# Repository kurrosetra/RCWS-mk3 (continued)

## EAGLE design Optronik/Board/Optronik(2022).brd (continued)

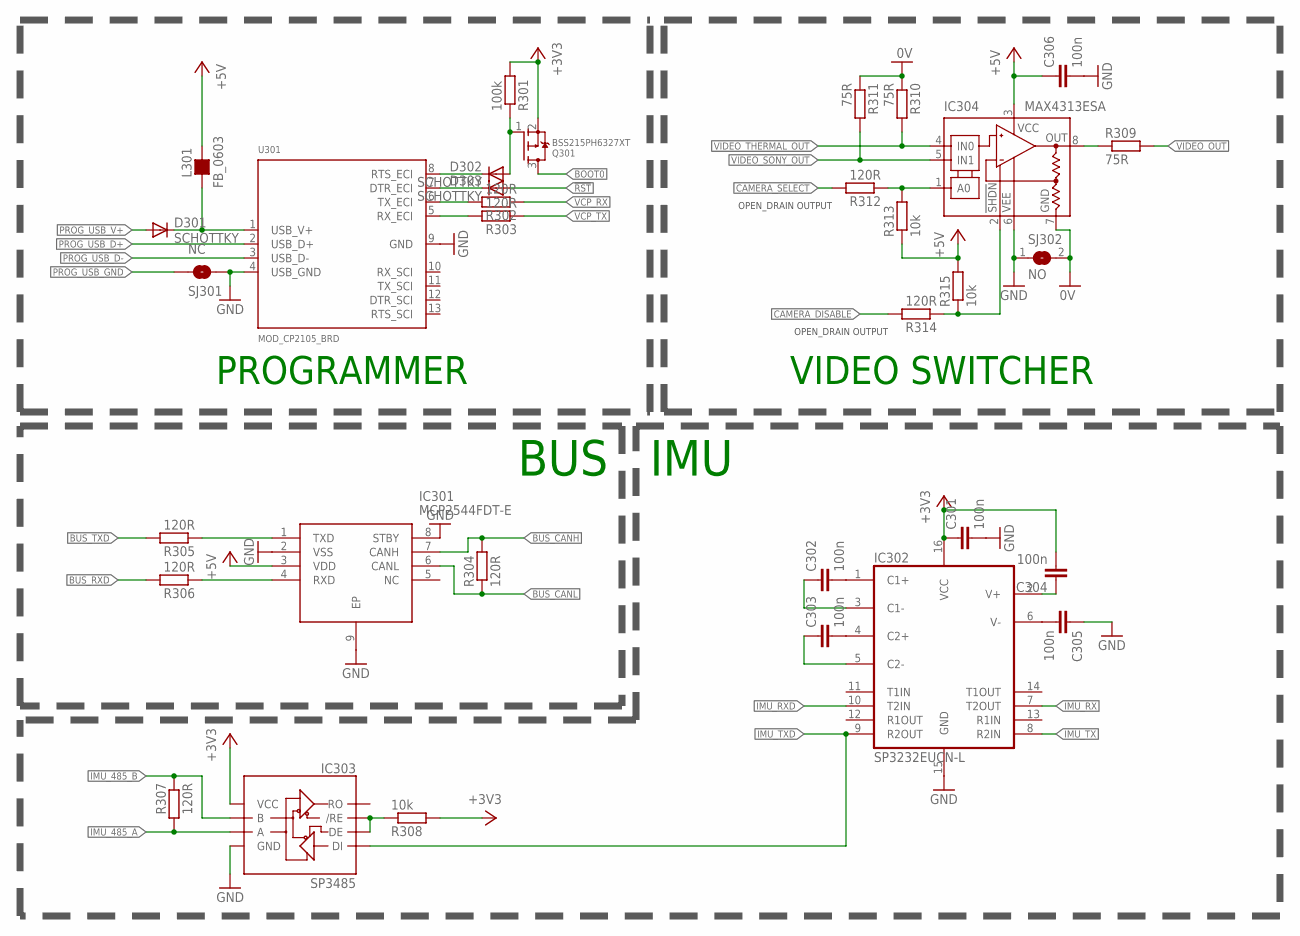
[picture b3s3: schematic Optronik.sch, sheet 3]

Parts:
C301, C302, C303, C304, C305, C306: 100n; C0603
D301, D302, D303: SCHOTTKY; MICROMELF-W
IC301: MCP2544FDT-E; TDFN-8
IC302: SP3232EUCN-L; SO016
IC303: SP3485; SO08
IC304: MAX4313ESA; SO08
L301: FB_0603; L0603
Q301: BSS215PH6327XT; SOT23-W
R301: 100k; R0603
R302, R303, R304, R305, R306, R307, R312, R314: 120R; R0603
R308, R313, R315: 10k; R0603
R309, R310, R311: 75R; R0603
SJ301: NC; SJ_2S-TRACE_THICK
SJ302: NO; SJS
U301: MOD_CP2105_BRD; MOD_CP2105_BOARD

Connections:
0V: IC304.7 (GND), R310.1, R311.1, SJ302.2; also elsewhere on the board
!RST: D303.A; also elsewhere on the board
+3V3: C301.1, C304.2, IC302.16 (VCC), IC303.8 (VCC), Q301.2 (S), R301.2, R308.2; also elsewhere on the board
+5V: C306.1, IC301.3 (VDD), IC304.3 (V+), L301.2, R313.1, R315.2; also elsewhere on the board
BOOT0: Q301.3 (D); also elsewhere on the board
BUS_CANH: IC301.7 (CANH), R304.2; also elsewhere on the board
BUS_CANL: IC301.6 (CANL), R304.1; also elsewhere on the board
BUS_RXD: R306.2; also elsewhere on the board
BUS_TXD: R305.2; also elsewhere on the board
CAMERA_DISABLE: R314.2; also elsewhere on the board
CAMERA_SELECT: R312.2; also elsewhere on the board
GND: C301.2, C305.1, C306.2, IC301.2 (VSS), IC301.8 (STBY), IC301.9 (EP), IC302.15 (GND), IC303.5 (GND), IC304.6 (V-), SJ301.2, SJ302.1, U301.4 (USB_GND), U301.9 (GND); also elsewhere on the board
IMU_485_A: IC303.6 (A), R307.2; also elsewhere on the board
IMU_485_B: IC303.7 (B), R307.1; also elsewhere on the board
IMU_RX: IC302.7 (T2OUT); also elsewhere on the board
IMU_RXD: IC302.10 (T2IN); also elsewhere on the board
IMU_TX: IC302.8 (R2IN); also elsewhere on the board
IMU_TXD: IC302.9 (R2OUT), IC303.4 (DI); also elsewhere on the board
unnamed: IC303.2 (/RE), IC303.3 (DE), R308.1
unnamed: IC304.1 (A0), R312.1, R313.2
unnamed: IC301.1 (TXD), R305.1
unnamed: IC301.4 (RXD), R306.1
unnamed: R303.2, U301.5 (RX_ECI)
unnamed: R302.2, U301.6 (TX_ECI)
unnamed: D303.C, U301.7 (DTR_ECI)
unnamed: IC304.8 (OUT), R309.1
unnamed: D302.C, U301.8 (RTS_ECI)
unnamed: IC304.2 (!SHDN), R314.1, R315.1
unnamed: D301.C, L301.1, U301.1 (USB_V+)
unnamed: D302.A, Q301.1 (G), R301.1
unnamed: C305.2, IC302.6 (V-)
unnamed: C302.2, IC302.1 (C1+)
unnamed: C303.2, IC302.4 (C2+)
unnamed: C302.1, IC302.3 (C1-)
unnamed: C303.1, IC302.5 (C2-)
unnamed: C304.1, IC302.2 (V+)
PROG_USB_D+: U301.2 (USB_D+); also elsewhere on the board
PROG_USB_D-: U301.3 (USB_D-); also elsewhere on the board
PROG_USB_GND: SJ301.1; also elsewhere on the board
PROG_USB_V+: D301.A; also elsewhere on the board
VCP_RX: R302.1; also elsewhere on the board
VCP_TX: R303.1; also elsewhere on the board
VIDEO_OUT: R309.2; also elsewhere on the board
VIDEO_SONY_OUT: IC304.5 (IN1), R311.2; also elsewhere on the board
VIDEO_THERMAL_OUT: IC304.4 (IN0), R310.2; also elsewhere on the board

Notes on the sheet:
BUS
IMU
OPEN_DRAIN OUTPUT
PROGRAMMER
VIDEO SWITCHER

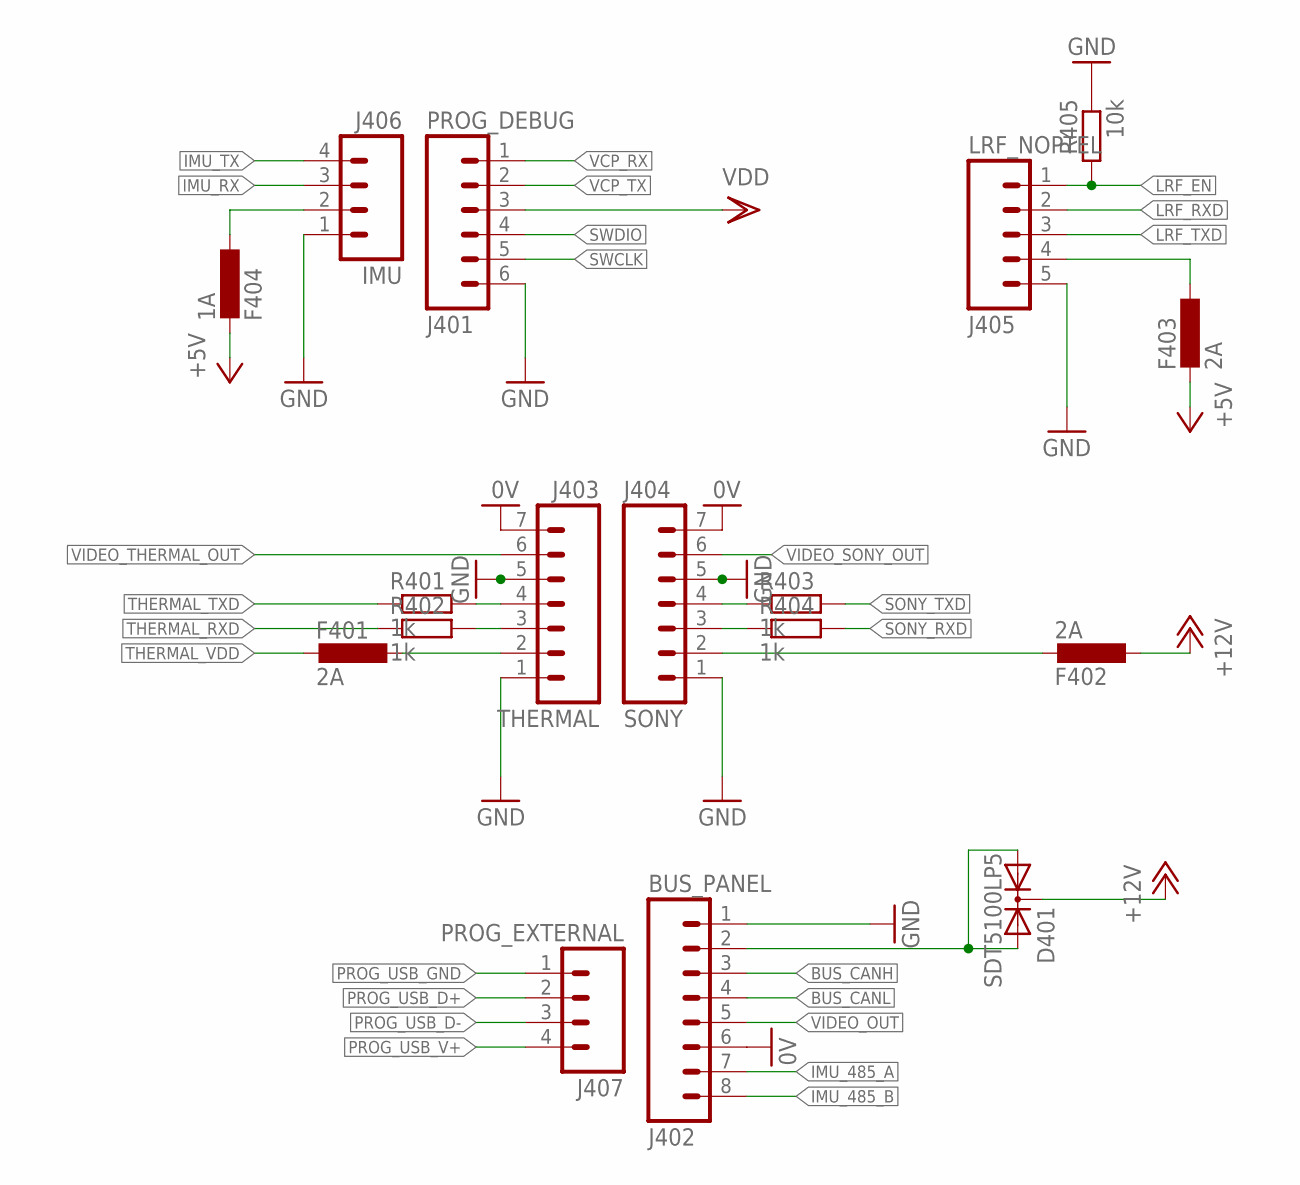
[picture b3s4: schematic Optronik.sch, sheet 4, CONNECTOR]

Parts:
D401: SDT5100LP5; POWERDI5-3
F401, F402, F403: 2A; L0805
F404: 1A; L0805
J401: PROG_DEBUG; XHS-6-VERT-SMD
J402: BUS_PANEL; XHS-8-RA
J403: THERMAL; XHS-7-RA
J404: SONY; XHS-7-RA
J405: LRF_NOPTEL; XHS-5-RA
J406: IMU; XHS-4-RA
J407: PROG_EXTERNAL; XHS-4-RA
R401, R402, R403, R404: 1k; R0603
R405: 10k; R0603

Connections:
0V: J402.6, J403.7, J404.7; also elsewhere on the board
!LRF_EN: J405.1, R405.2; also elsewhere on the board
+5V: F403.2, F404.2; also elsewhere on the board
+12V: D401.3, F402.1; also elsewhere on the board
BUS_CANH: J402.3; also elsewhere on the board
BUS_CANL: J402.4; also elsewhere on the board
GND: J401.6, J402.1, J403.1, J403.5, J404.1, J404.5, J405.5, J406.1, R405.1; also elsewhere on the board
IMU_485_A: J402.7; also elsewhere on the board
IMU_485_B: J402.8; also elsewhere on the board
IMU_RX: J406.3; also elsewhere on the board
IMU_TX: J406.4; also elsewhere on the board
LRF_RXD: J405.2; also elsewhere on the board
LRF_TXD: J405.3; also elsewhere on the board
unnamed: F403.1, J405.4
unnamed: F402.2, J404.2
unnamed: J403.4, R401.2
unnamed: F401.1, J403.2
unnamed: J403.3, R402.2
unnamed: J404.4, R403.1
unnamed: J404.3, R404.1
unnamed: F404.1, J406.2
PROG_USB_D+: J407.2; also elsewhere on the board
PROG_USB_D-: J407.3; also elsewhere on the board
PROG_USB_GND: J407.1; also elsewhere on the board
PROG_USB_V+: J407.4; also elsewhere on the board
RAW_12V: D401.1, D401.2, J402.2
SONY_RXD: R404.2; also elsewhere on the board
SONY_TXD: R403.2; also elsewhere on the board
SWCLK: J401.5; also elsewhere on the board
SWDIO: J401.4; also elsewhere on the board
THERMAL_RXD: R402.1; also elsewhere on the board
THERMAL_TXD: R401.1; also elsewhere on the board
THERMAL_VDD: F401.2; also elsewhere on the board
VCP_RX: J401.1; also elsewhere on the board
VCP_TX: J401.2; also elsewhere on the board
VDD: J401.3; also elsewhere on the board
VIDEO_OUT: J402.5; also elsewhere on the board
VIDEO_SONY_OUT: J404.6; also elsewhere on the board
VIDEO_THERMAL_OUT: J403.6; also elsewhere on the board

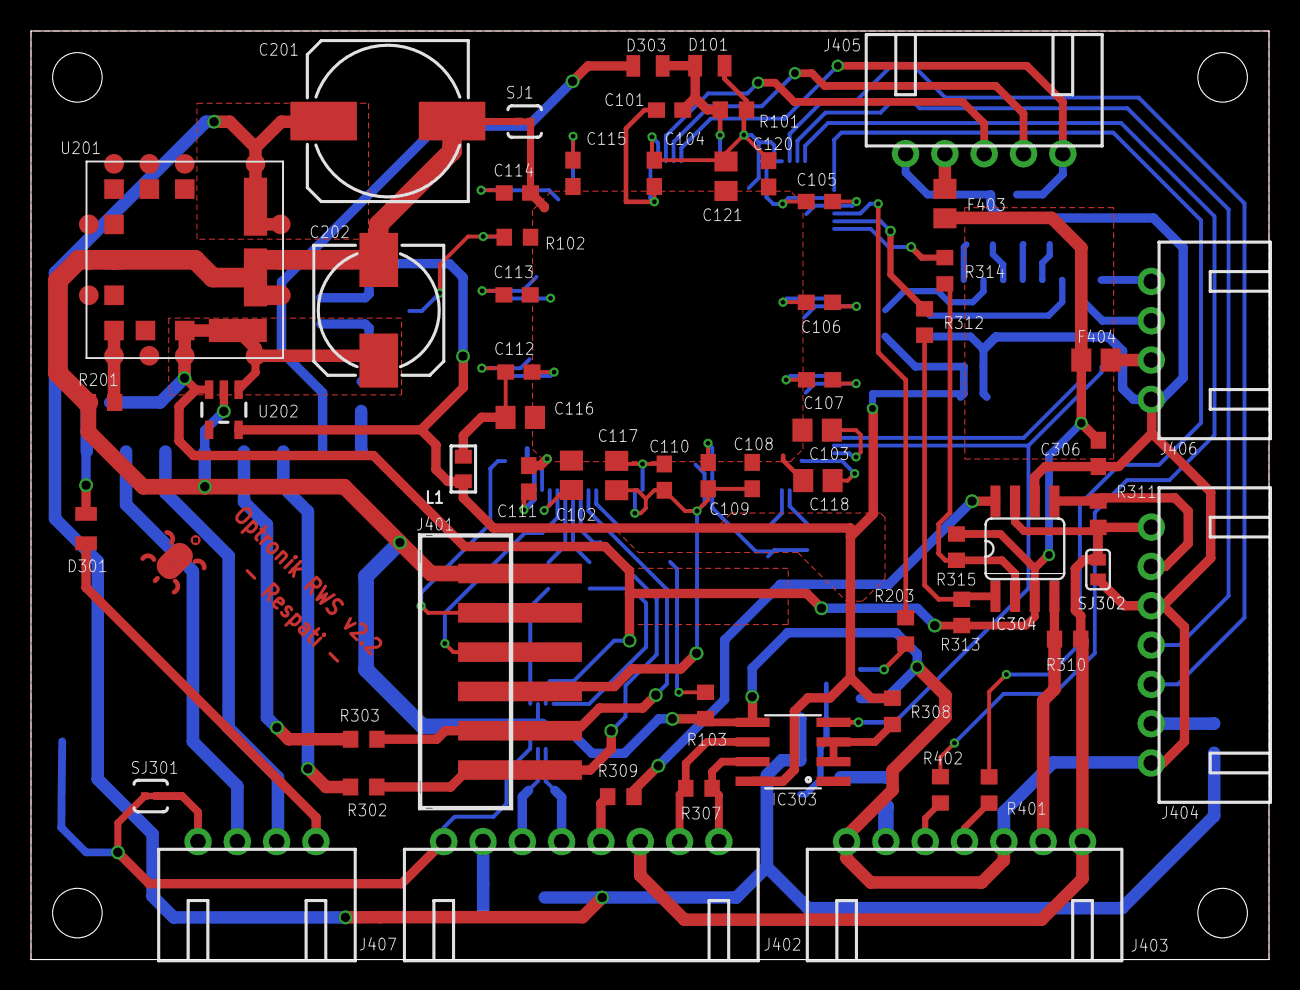
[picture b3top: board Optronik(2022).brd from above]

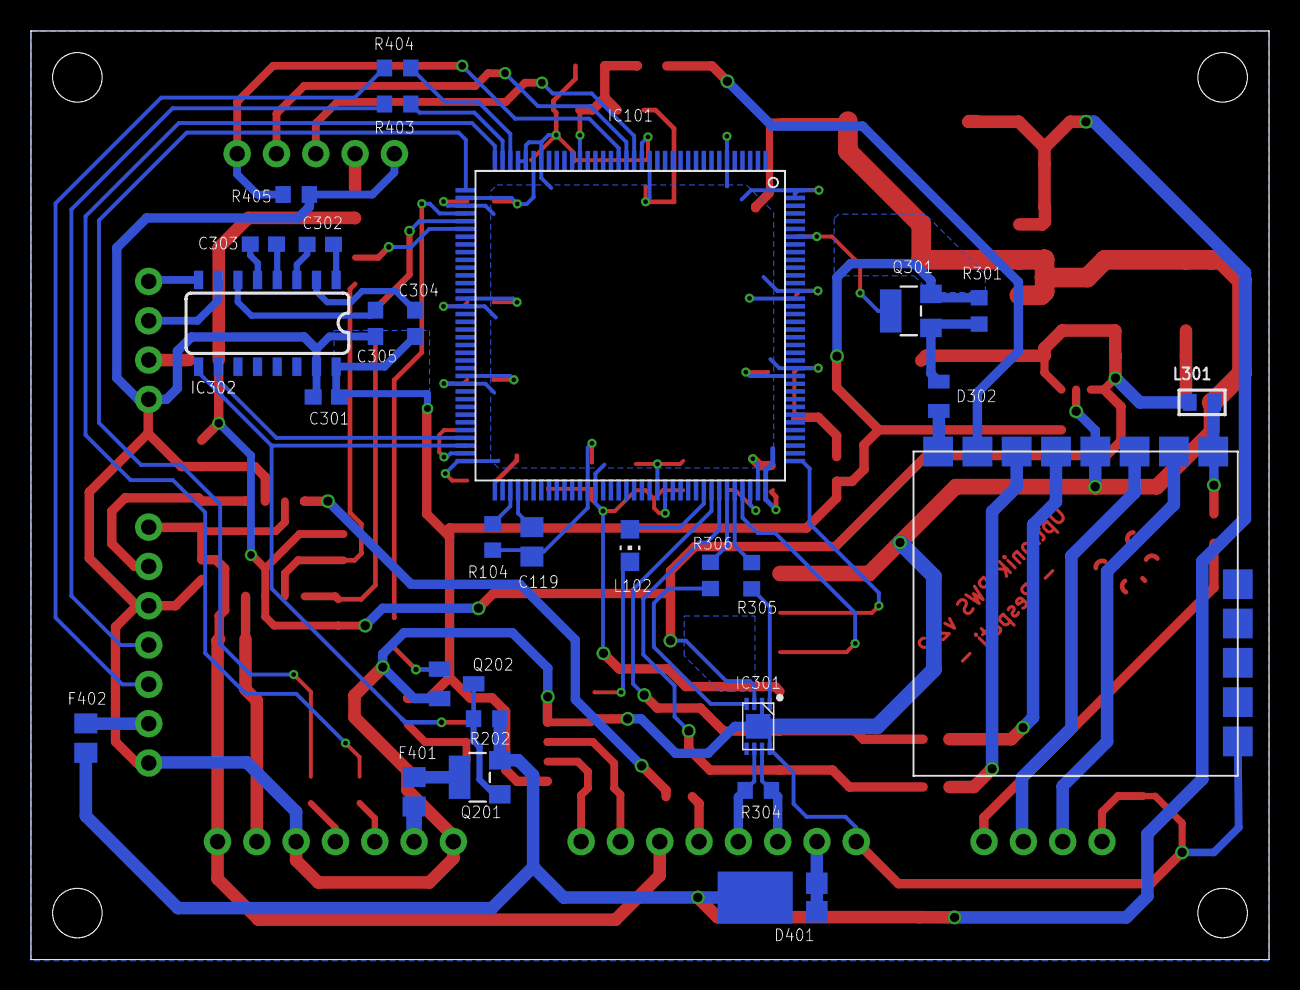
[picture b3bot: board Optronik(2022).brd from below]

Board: 2 copper layers, 80.0 x 60.0 mm, 90 parts (29 on the bottom side), 77 nets.

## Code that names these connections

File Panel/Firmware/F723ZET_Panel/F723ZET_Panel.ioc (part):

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Mcu.Name=STM32F723Z(C-E)Tx
Mcu.Package=LQFP144
Mcu.UserName=STM32F723ZETx
PA0-WKUP.GPIOParameters=GPIO_PuPd,GPIO_Label
PA0-WKUP.GPIO_Label=JSR_B
PA0-WKUP.GPIO_PuPd=GPIO_PULLUP
PA0-WKUP.Signal=GPIO_Input
PA1.GPIOParameters=GPIO_PuPd,GPIO_Label
PA1.GPIO_Label=JSR_TRIG
PA1.GPIO_PuPd=GPIO_PULLUP
PA1.Signal=GPIO_Input
PA10.GPIOParameters=GPIO_Label
PA10.GPIO_Label=VCP_RX
PA10.Mode=Asynchronous
PA10.Signal=USART1_RX
PA13.Mode=Serial_Wire
PA13.Signal=SYS_JTMS-SWDIO
PA14.Mode=Serial_Wire
PA14.Signal=SYS_JTCK-SWCLK
PA15.GPIOParameters=GPIO_Label
PA15.GPIO_Label=V_BATT_FREQ
PA15.Signal=S_TIM2_CH1_ETR
PA2.GPIOParameters=GPIO_Label
PA2.GPIO_Label=PC_S_RXD
PA2.Mode=Asynchronous
PA2.Signal=USART2_TX
PA3.GPIOParameters=GPIO_PuPd,GPIO_Label
PA3.GPIO_Label=PC_S_TXD
PA3.GPIO_PuPd=GPIO_PULLUP
PA3.Mode=Asynchronous
PA3.Signal=USART2_RX
PA4.GPIOParameters=GPIO_PuPd,GPIO_Label
PA4.GPIO_Label=JSL_DEADMAN
PA4.GPIO_PuPd=GPIO_PULLUP
PA4.Signal=GPIO_Input
PA5.GPIOParameters=GPIO_Label
PA5.GPIO_Label=JSL_AZIMUTH
PA5.Signal=ADCx_IN5
PA6.GPIOParameters=GPIO_Label
PA6.GPIO_Label=JSL_ELEVATION
PA6.Signal=ADCx_IN6
PA7.GPIOParameters=GPIO_PuPd,GPIO_Label
PA7.GPIO_Label=JSL_A
PA7.GPIO_PuPd=GPIO_PULLUP
PA7.Signal=GPIO_Input
PA8.GPIOParameters=GPIO_Label
PA8.GPIO_Label=LED_BUILTIN
PA8.Signal=GPIO_Output
PA9.GPIOParameters=GPIO_Label
PA9.GPIO_Label=VCP_TX
PA9.Mode=Asynchronous
PA9.Signal=USART1_TX
PB10.GPIOParameters=GPIO_Label
PB10.GPIO_Label=PC_E_RXD
PB10.Mode=Asynchronous
PB10.Signal=USART3_TX
PB11.GPIOParameters=GPIO_PuPd,GPIO_Label
PB11.GPIO_Label=PC_E_TXD
PB11.GPIO_PuPd=GPIO_PULLUP
PB11.Mode=Asynchronous
PB11.Signal=USART3_RX
PB2.Signal=QUADSPI_CLK
PB3.GPIOParameters=PinState,GPIO_PuPd,GPIO_Label,GPIO_ModeDefaultOutputPP
PB3.GPIO_Label=SLA_POWER_ENABLE
PB3.GPIO_ModeDefaultOutputPP=GPIO_MODE_OUTPUT_OD
PB3.GPIO_PuPd=GPIO_NOPULL
PB3.PinState=GPIO_PIN_SET
PB3.Signal=GPIO_Output
PB4.GPIOParameters=GPIO_PuPd,GPIO_Label
PB4.GPIO_Label=DUAL_TRIG_IN
PB4.GPIO_PuPd=GPIO_PULLUP
PB4.Signal=GPIO_Input
PB5.GPIOParameters=GPIO_Label
PB5.GPIO_Label=TRIG_PULSE_OUT
PB5.Signal=GPIO_Output
PB6.Signal=QUADSPI_BK1_NCS
PB8.Mode=CAN_Activate
PB8.Signal=CAN1_RX
PB9.Mode=CAN_Activate
PB9.Signal=CAN1_TX
PC0.GPIOParameters=GPIO_PuPd,GPIO_Label
PC0.GPIO_Label=JSR_DEADMAN
PC0.GPIO_PuPd=GPIO_PULLUP
PC0.Signal=GPIO_Input
PC1.GPIOParameters=GPIO_Label
PC1.GPIO_Label=JSR_AZIMUTH
PC1.Signal=ADCx_IN11
PC10.GPIOParameters=GPIO_Label
PC10.GPIO_Label=BMS_RXD
PC10.Signal=UART4_TX
PC11.GPIOParameters=GPIO_Label
PC11.GPIO_Label=BMS_TXD
PC11.Signal=UART4_RX
PC13.GPIOParameters=GPIO_Label
PC13.GPIO_Label=SYS_WKUP4
PC13.Signal=SYS_WKUP4
PC2.GPIOParameters=GPIO_Label
PC2.GPIO_Label=JSR_ELEVATION
PC2.Signal=ADCx_IN12
PC3.GPIOParameters=GPIO_PuPd,GPIO_Label
PC3.GPIO_Label=JSR_A
PC3.GPIO_PuPd=GPIO_PULLUP
PC3.Signal=GPIO_Input
PC4.GPIOParameters=GPIO_PuPd,GPIO_Label
PC4.GPIO_Label=JSL_B
PC4.GPIO_PuPd=GPIO_PULLUP
PC4.Signal=GPIO_Input
PC5.GPIOParameters=GPIO_PuPd,GPIO_Label
PC5.GPIO_Label=JSL_TRIG
PC5.GPIO_PuPd=GPIO_PULLUP
PC5.Signal=GPIO_Input
PC6.GPIOParameters=GPIO_Label
PC6.GPIO_Label=OUT_TRIGGER
PC6.Signal=GPIO_Output
PC7.GPIOParameters=GPIO_Label
PC7.GPIO_Label=OUT_POWER
PC7.Signal=GPIO_Output
PC8.GPIOParameters=GPIO_Label
PC8.GPIO_Label=OUT_CAMERA_SELECT
PC8.Signal=GPIO_Output
PC9.GPIOParameters=GPIO_Label
PC9.GPIO_Label=OUT_LRF_ENABLE
PC9.Signal=GPIO_Output
PD0.GPIOParameters=GPIO_PuPd,GPIO_Label
PD0.GPIO_Label=IN_LRF_START
PD0.GPIO_PuPd=GPIO_PULLUP
PD0.Signal=GPIO_Input
PD1.GPIOParameters=GPIO_PuPd,GPIO_Label
PD1.GPIO_Label=IN_LRF_MAN_UP
PD1.GPIO_PuPd=GPIO_PULLUP
PD1.Signal=GPIO_Input
PD2.GPIOParameters=GPIO_PuPd,GPIO_Label
PD2.GPIO_Label=IN_TRIGGER_ENABLE
PD2.GPIO_PuPd=GPIO_PULLUP
PD2.Signal=GPIO_Input
PD3.GPIOParameters=GPIO_PuPd,GPIO_Label
PD3.GPIO_Label=IN_FOCUS_FAR
PD3.GPIO_PuPd=GPIO_PULLUP
PD3.Signal=GPIO_Input
PD4.GPIOParameters=GPIO_PuPd,GPIO_Label
PD4.GPIO_Label=IN_TARGET_NEXT
PD4.GPIO_PuPd=GPIO_PULLUP
PD4.Signal=GPIO_Input
PD5.GPIOParameters=GPIO_PuPd,GPIO_Label
PD5.GPIO_Label=IN_FIRE_MODE1
PD5.GPIO_PuPd=GPIO_PULLUP
PD5.Signal=GPIO_Input
PD6.GPIOParameters=GPIO_PuPd,GPIO_Label
PD6.GPIO_Label=IN_SPD1
PD6.GPIO_PuPd=GPIO_PULLUP
PD6.Signal=GPIO_Input
PD7.GPIOParameters=GPIO_PuPd,GPIO_Label
PD7.GPIO_Label=IN_SPD0
PD7.GPIO_PuPd=GPIO_PULLUP
PD7.Signal=GPIO_Input
PF6.Signal=QUADSPI_BK1_IO3
PF7.Signal=QUADSPI_BK1_IO2
PF8.Signal=QUADSPI_BK1_IO0
PF9.Signal=QUADSPI_BK1_IO1
PG10.GPIOParameters=GPIO_PuPd,GPIO_Label
PG10.GPIO_Label=IN_TARGET_PREV
PG10.GPIO_PuPd=GPIO_PULLUP
PG10.Signal=GPIO_Input
PG11.GPIOParameters=GPIO_PuPd,GPIO_Label
PG11.GPIO_Label=IN_FOCUS_NEAR
PG11.GPIO_PuPd=GPIO_PULLUP
PG11.Signal=GPIO_Input
PG12.GPIOParameters=GPIO_PuPd,GPIO_Label
PG12.GPIO_Label=IN_CAMERA_SELECT
PG12.GPIO_PuPd=GPIO_PULLUP
PG12.Signal=GPIO_Input
PG13.GPIOParameters=GPIO_PuPd,GPIO_Label
PG13.GPIO_Label=IN_LRF_MAN_DOWN
PG13.GPIO_PuPd=GPIO_PULLUP
PG13.Signal=GPIO_Input
PG14.GPIOParameters=GPIO_PuPd,GPIO_Label
PG14.GPIO_Label=IN_LRF_ENABLE
PG14.GPIO_PuPd=GPIO_PULLUP
PG14.Signal=GPIO_Input
PG15.GPIOParameters=GPIO_PuPd,GPIO_Label
PG15.GPIO_Label=IN_RESV
PG15.GPIO_PuPd=GPIO_PULLUP
PG15.Signal=GPIO_Input
PG8.GPIOParameters=GPIO_PuPd,GPIO_Label
PG8.GPIO_Label=OUT_RESV
PG8.GPIO_PuPd=GPIO_PULLUP
PG8.Signal=GPIO_Input
PG9.GPIOParameters=GPIO_PuPd,GPIO_Label
PG9.GPIO_Label=IN_FIRE_MODE0
PG9.GPIO_PuPd=GPIO_PULLUP
PG9.Signal=GPIO_Input
PH0-OSC_IN.Mode=HSE-External-Oscillator
PH0-OSC_IN.Signal=RCC_OSC_IN
PH1-OSC_OUT.Mode=HSE-External-Oscillator
PH1-OSC_OUT.Signal=RCC_OSC_OUT
RCC.HSE_VALUE=8000000
RCC.SYSCLKFreq_VALUE=216000000
RCC.SYSCLKSource=RCC_SYSCLKSOURCE_PLLCLK
board=custom

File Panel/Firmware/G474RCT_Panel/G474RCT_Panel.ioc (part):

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Mcu.Name=STM32G474R(B-C-E)Tx
Mcu.Package=LQFP64
Mcu.UserName=STM32G474RCTx
PA1.GPIOParameters=GPIO_Label
PA1.GPIO_Label=V_BATT_SCALED
PA1.Signal=SharedAnalog_PA1
PA10.GPIOParameters=GPIO_Speed,GPIO_PuPd,GPIO_Label
PA10.GPIO_Label=VCP_RX
PA10.GPIO_PuPd=GPIO_PULLUP
PA10.GPIO_Speed=GPIO_SPEED_FREQ_VERY_HIGH
PA10.Mode=Asynchronous
PA10.Signal=USART1_RX
PA11.GPIOParameters=GPIO_Speed,GPIO_PuPd,GPIO_Label
PA11.GPIO_Label=BUS_FDCAN_RX
PA11.GPIO_PuPd=GPIO_PULLUP
PA11.GPIO_Speed=GPIO_SPEED_FREQ_VERY_HIGH
PA11.Mode=FDCAN_Activate
PA11.Signal=FDCAN1_RX
PA12.GPIOParameters=GPIO_Speed,GPIO_PuPd,GPIO_Label
PA12.GPIO_Label=BUS_FDCAN_TX
PA12.GPIO_PuPd=GPIO_PULLUP
PA12.GPIO_Speed=GPIO_SPEED_FREQ_VERY_HIGH
PA12.Mode=FDCAN_Activate
PA12.Signal=FDCAN1_TX
PA13.GPIOParameters=GPIO_Label
PA13.GPIO_Label=SWDIO
PA13.Mode=Serial_Wire
PA13.Signal=SYS_JTMS-SWDIO
PA14.GPIOParameters=GPIO_Label
PA14.GPIO_Label=SWCLK
PA14.Mode=Serial_Wire
PA14.Signal=SYS_JTCK-SWCLK
PA15.GPIOParameters=GPIO_PuPd,GPIO_Label
PA15.GPIO_Label=JSL_TRIG
PA15.GPIO_PuPd=GPIO_PULLUP
PA15.Signal=GPIO_Input
PA2.GPIOParameters=GPIO_Speed,GPIO_Label
PA2.GPIO_Label=XROM_NCS
PA2.GPIO_Speed=GPIO_SPEED_FREQ_VERY_HIGH
PA2.Signal=QUADSPI1_BK1_NCS
PA3.GPIOParameters=GPIO_Speed,GPIO_Label
PA3.GPIO_Label=XROM_CLK
PA3.GPIO_Speed=GPIO_SPEED_FREQ_VERY_HIGH
PA3.Signal=QUADSPI1_CLK
PA6.GPIOParameters=GPIO_Speed,GPIO_Label
PA6.GPIO_Label=XROM_IO3
PA6.GPIO_Speed=GPIO_SPEED_FREQ_VERY_HIGH
PA6.Signal=QUADSPI1_BK1_IO3
PA7.GPIOParameters=GPIO_Speed,GPIO_Label
PA7.GPIO_Label=XROM_IO2
PA7.GPIO_Speed=GPIO_SPEED_FREQ_VERY_HIGH
PA7.Signal=QUADSPI1_BK1_IO2
PA8.GPIOParameters=GPIO_PuPd,GPIO_Label
PA8.GPIO_Label=JSL_B
PA8.GPIO_PuPd=GPIO_PULLUP
PA8.Signal=GPIO_Input
PA9.GPIOParameters=GPIO_Speed,GPIO_Label
PA9.GPIO_Label=VCP_TX
PA9.GPIO_Speed=GPIO_SPEED_FREQ_VERY_HIGH
PA9.Mode=Asynchronous
PA9.Signal=USART1_TX
PB0.GPIOParameters=GPIO_Speed,GPIO_Label
PB0.GPIO_Label=XROM_IO1
PB0.GPIO_Speed=GPIO_SPEED_FREQ_VERY_HIGH
PB0.Signal=QUADSPI1_BK1_IO1
PB1.GPIOParameters=GPIO_Speed,GPIO_Label
PB1.GPIO_Label=XROM_IO0
PB1.GPIO_Speed=GPIO_SPEED_FREQ_VERY_HIGH
PB1.Signal=QUADSPI1_BK1_IO0
PB10.GPIOParameters=GPIO_Speed,GPIO_PuPd,GPIO_Label
PB10.GPIO_Label=PC_TXD
PB10.GPIO_PuPd=GPIO_PULLUP
PB10.GPIO_Speed=GPIO_SPEED_FREQ_VERY_HIGH
PB10.Mode=Asynchronous
PB10.Signal=LPUART1_RX
PB11.GPIOParameters=GPIO_Speed,GPIO_PuPd,GPIO_Label
PB11.GPIO_Label=PC_RXD
PB11.GPIO_PuPd=GPIO_NOPULL
PB11.GPIO_Speed=GPIO_SPEED_FREQ_VERY_HIGH
PB11.Mode=Asynchronous
PB11.Signal=LPUART1_TX
PB12.GPIOParameters=GPIO_Label
PB12.GPIO_Label=OTHER_CAN_RX
PB12.Signal=FDCAN2_RX
PB13.GPIOParameters=GPIO_Label
PB13.GPIO_Label=OTHER_CAN_TX
PB13.Signal=FDCAN2_TX
PB14.GPIOParameters=GPIO_PuPd,GPIO_Label
PB14.GPIO_Label=JSR_DEADMAN
PB14.GPIO_PuPd=GPIO_PULLUP
PB14.Signal=GPIO_Input
PB15.GPIOParameters=GPIO_PuPd,GPIO_Label
PB15.GPIO_Label=JSR_A
PB15.GPIO_PuPd=GPIO_PULLUP
PB15.Signal=GPIO_Input
PB3.GPIOParameters=GPIO_Speed,GPIO_PuPd,GPIO_Label
PB3.GPIO_Label=BUTTON_RXD
PB3.GPIO_PuPd=GPIO_PULLUP
PB3.GPIO_Speed=GPIO_SPEED_FREQ_VERY_HIGH
PB3.Mode=Asynchronous
PB3.Signal=USART2_TX
PB4.GPIOParameters=GPIO_Speed,GPIO_PuPd,GPIO_Label
PB4.GPIO_Label=BUTTON_TXD
PB4.GPIO_PuPd=GPIO_PULLUP
PB4.GPIO_Speed=GPIO_SPEED_FREQ_VERY_HIGH
PB4.Mode=Asynchronous
PB4.Signal=USART2_RX
PB6.GPIOParameters=GPIO_Speed,GPIO_Label
PB6.GPIO_Label=LED_BUILTIN
PB6.GPIO_Speed=GPIO_SPEED_FREQ_VERY_HIGH
PB6.Signal=S_TIM4_CH1
PB7.GPIOParameters=GPIO_Speed,GPIO_Label,GPIO_FM7
PB7.GPIO_FM7=SYSCFG_FASTMODEPLUS_PB7
PB7.GPIO_Label=TRIG_PULSE_OUT
PB7.GPIO_Speed=GPIO_SPEED_FREQ_VERY_HIGH
PB7.Signal=S_TIM4_CH2
PB8-BOOT0.GPIOParameters=GPIO_Label
PB8-BOOT0.GPIO_Label=BOOT0
PB8-BOOT0.Signal=GPIO_Input
PC0.GPIOParameters=GPIO_Label
PC0.GPIO_Label=JSL_AZIMUTH
PC0.Mode=IN6-Single-Ended
PC0.Signal=ADC2_IN6
PC1.GPIOParameters=GPIO_Label
PC1.GPIO_Label=JSL_ELEVATION
PC1.Mode=IN7-Single-Ended
PC1.Signal=ADC2_IN7
PC13.Signal=SYS_WKUP2
PC14-OSC32_IN.GPIOParameters=GPIO_PuPd,GPIO_Label
PC14-OSC32_IN.GPIO_Label=SLA_POWER_EN
PC14-OSC32_IN.GPIO_PuPd=GPIO_PULLDOWN
PC14-OSC32_IN.Signal=GPIO_Output
PC4.GPIOParameters=GPIO_Label
PC4.GPIO_Label=JSR_AZIMUTH
PC4.Mode=IN5-Single-Ended
PC4.Signal=ADC2_IN5
PC5.GPIOParameters=GPIO_Label
PC5.GPIO_Label=JSR_ELEVATION
PC5.Mode=IN11-Single-Ended
PC5.Signal=ADC2_IN11
PC6.GPIOParameters=GPIO_PuPd,GPIO_Label
PC6.GPIO_Label=JSR_B
PC6.GPIO_PuPd=GPIO_PULLUP
PC6.Signal=GPIO_Input
PC7.GPIOParameters=GPIO_PuPd,GPIO_Label
PC7.GPIO_Label=JSR_TRIG
PC7.GPIO_PuPd=GPIO_PULLUP
PC7.Signal=GPIO_Input
PC8.GPIOParameters=GPIO_PuPd,GPIO_Label
PC8.GPIO_Label=JSL_DEADMAN
PC8.GPIO_PuPd=GPIO_PULLUP
PC8.Signal=GPIO_Input
PC9.GPIOParameters=GPIO_PuPd,GPIO_Label
PC9.GPIO_Label=JSL_A
PC9.GPIO_PuPd=GPIO_PULLUP
PC9.Signal=GPIO_Input
PF0-OSC_IN.Mode=HSE-External-Oscillator
PF0-OSC_IN.Signal=RCC_OSC_IN
PF1-OSC_OUT.Mode=HSE-External-Oscillator
PF1-OSC_OUT.Signal=RCC_OSC_OUT
RCC.HSE_VALUE=8000000
RCC.SYSCLKFreq_VALUE=170000000
RCC.SYSCLKSource=RCC_SYSCLKSOURCE_PLLCLK
board=custom

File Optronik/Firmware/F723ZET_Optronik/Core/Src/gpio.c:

/* USER CODE BEGIN Header */
/**
  ******************************************************************************
  * @file    gpio.c
  * @brief   This file provides code for the configuration
  *          of all used GPIO pins.
  ******************************************************************************
  * @attention
  *
  * Copyright (c) 2022 STMicroelectronics.
  * All rights reserved.
  *
  * This software is licensed under terms that can be found in the LICENSE file
  * in the root directory of this software component.
  * If no LICENSE file comes with this software, it is provided AS-IS.
  *
  ******************************************************************************
  */
/* USER CODE END Header */

/* Includes ------------------------------------------------------------------*/
#include "gpio.h"

/* USER CODE BEGIN 0 */

/* USER CODE END 0 */

/*----------------------------------------------------------------------------*/
/* Configure GPIO                                                             */
/*----------------------------------------------------------------------------*/
/* USER CODE BEGIN 1 */

/* USER CODE END 1 */

/** Configure pins
     PF6   ------> UART7_RX
     PF7   ------> UART7_TX
     PB10   ------> USART3_TX
     PB11   ------> USART3_RX
*/
void MX_GPIO_Init(void)
{

  GPIO_InitTypeDef GPIO_InitStruct = {0};

  /* GPIO Ports Clock Enable */
  __HAL_RCC_GPIOE_CLK_ENABLE();
  __HAL_RCC_GPIOC_CLK_ENABLE();
  __HAL_RCC_GPIOF_CLK_ENABLE();
  __HAL_RCC_GPIOH_CLK_ENABLE();
  __HAL_RCC_GPIOA_CLK_ENABLE();
  __HAL_RCC_GPIOB_CLK_ENABLE();
  __HAL_RCC_GPIOG_CLK_ENABLE();
  __HAL_RCC_GPIOD_CLK_ENABLE();

  /*Configure GPIO pin Output Level */
  HAL_GPIO_WritePin(LRF_EN_GPIO_Port, LRF_EN_Pin, GPIO_PIN_RESET);

  /*Configure GPIO pin Output Level */
  HAL_GPIO_WritePin(GPIOA, THERMAL_PWR_EN_Pin|LED_BUILTIN_Pin, GPIO_PIN_RESET);

  /*Configure GPIO pin Output Level */
  HAL_GPIO_WritePin(GPIOA, CAMERA_SELECT_Pin|CAMERA_ENABLE_Pin, GPIO_PIN_SET);

  /*Configure GPIO pins : PE2 PE3 PE4 PE5
                           PE6 PE7 PE8 PE9
                           PE10 PE11 PE12 PE13
                           PE14 PE15 PE0 PE1 */
  GPIO_InitStruct.Pin = GPIO_PIN_2|GPIO_PIN_3|GPIO_PIN_4|GPIO_PIN_5
                          |GPIO_PIN_6|GPIO_PIN_7|GPIO_PIN_8|GPIO_PIN_9
                          |GPIO_PIN_10|GPIO_PIN_11|GPIO_PIN_12|GPIO_PIN_13
                          |GPIO_PIN_14|GPIO_PIN_15|GPIO_PIN_0|GPIO_PIN_1;
  GPIO_InitStruct.Mode = GPIO_MODE_ANALOG;
  GPIO_InitStruct.Pull = GPIO_NOPULL;
  HAL_GPIO_Init(GPIOE, &GPIO_InitStruct);

  /*Configure GPIO pins : PC13 PC14 PC15 PC0
                           PC1 PC2 PC3 PC4
                           PC5 PC6 PC7 PC8
                           PC9 PC10 PC11 PC12 */
  GPIO_InitStruct.Pin = GPIO_PIN_13|GPIO_PIN_14|GPIO_PIN_15|GPIO_PIN_0
                          |GPIO_PIN_1|GPIO_PIN_2|GPIO_PIN_3|GPIO_PIN_4
                          |GPIO_PIN_5|GPIO_PIN_6|GPIO_PIN_7|GPIO_PIN_8
                          |GPIO_PIN_9|GPIO_PIN_10|GPIO_PIN_11|GPIO_PIN_12;
  GPIO_InitStruct.Mode = GPIO_MODE_ANALOG;
  GPIO_InitStruct.Pull = GPIO_NOPULL;
  HAL_GPIO_Init(GPIOC, &GPIO_InitStruct);

  /*Configure GPIO pins : PF0 PF1 PF2 PF3
                           PF4 PF5 PF9 PF10
                           PF11 PF12 PF13 PF14
                           PF15 */
  GPIO_InitStruct.Pin = GPIO_PIN_0|GPIO_PIN_1|GPIO_PIN_2|GPIO_PIN_3
                          |GPIO_PIN_4|GPIO_PIN_5|GPIO_PIN_9|GPIO_PIN_10
                          |GPIO_PIN_11|GPIO_PIN_12|GPIO_PIN_13|GPIO_PIN_14
                          |GPIO_PIN_15;
  GPIO_InitStruct.Mode = GPIO_MODE_ANALOG;
  GPIO_InitStruct.Pull = GPIO_NOPULL;
  HAL_GPIO_Init(GPIOF, &GPIO_InitStruct);

  /*Configure GPIO pin : PtPin */
  GPIO_InitStruct.Pin = LRF_TXD_Pin;
  GPIO_InitStruct.Mode = GPIO_MODE_AF_PP;
  GPIO_InitStruct.Pull = GPIO_PULLUP;
  GPIO_InitStruct.Speed = GPIO_SPEED_FREQ_VERY_HIGH;
  GPIO_InitStruct.Alternate = GPIO_AF8_UART7;
  HAL_GPIO_Init(LRF_TXD_GPIO_Port, &GPIO_InitStruct);

  /*Configure GPIO pin : PtPin */
  GPIO_InitStruct.Pin = LRF_RXD_Pin;
  GPIO_InitStruct.Mode = GPIO_MODE_AF_PP;
  GPIO_InitStruct.Pull = GPIO_NOPULL;
  GPIO_InitStruct.Speed = GPIO_SPEED_FREQ_VERY_HIGH;
  GPIO_InitStruct.Alternate = GPIO_AF8_UART7;
  HAL_GPIO_Init(LRF_RXD_GPIO_Port, &GPIO_InitStruct);

  /*Configure GPIO pin : PtPin */
  GPIO_InitStruct.Pin = LRF_EN_Pin;
  GPIO_InitStruct.Mode = GPIO_MODE_OUTPUT_PP;
  GPIO_InitStruct.Pull = GPIO_NOPULL;
  GPIO_InitStruct.Speed = GPIO_SPEED_FREQ_LOW;
  HAL_GPIO_Init(LRF_EN_GPIO_Port, &GPIO_InitStruct);

  /*Configure GPIO pins : PH0 PH1 */
  GPIO_InitStruct.Pin = GPIO_PIN_0|GPIO_PIN_1;
  GPIO_InitStruct.Mode = GPIO_MODE_ANALOG;
  GPIO_InitStruct.Pull = GPIO_NOPULL;
  HAL_GPIO_Init(GPIOH, &GPIO_InitStruct);

  /*Configure GPIO pin : PtPin */
  GPIO_InitStruct.Pin = THERMAL_PWR_EN_Pin;
  GPIO_InitStruct.Mode = GPIO_MODE_OUTPUT_PP;
  GPIO_InitStruct.Pull = GPIO_PULLDOWN;
  GPIO_InitStruct.Speed = GPIO_SPEED_FREQ_LOW;
  HAL_GPIO_Init(THERMAL_PWR_EN_GPIO_Port, &GPIO_InitStruct);

  /*Configure GPIO pins : PAPin PAPin */
  GPIO_InitStruct.Pin = CAMERA_SELECT_Pin|LED_BUILTIN_Pin;
  GPIO_InitStruct.Mode = GPIO_MODE_OUTPUT_PP;
  GPIO_InitStruct.Pull = GPIO_NOPULL;
  GPIO_InitStruct.Speed = GPIO_SPEED_FREQ_LOW;
  HAL_GPIO_Init(GPIOA, &GPIO_InitStruct);

  /*Configure GPIO pin : PtPin */
  GPIO_InitStruct.Pin = CAMERA_ENABLE_Pin;
  GPIO_InitStruct.Mode = GPIO_MODE_OUTPUT_OD;
  GPIO_InitStruct.Pull = GPIO_NOPULL;
  GPIO_InitStruct.Speed = GPIO_SPEED_FREQ_LOW;
  HAL_GPIO_Init(CAMERA_ENABLE_GPIO_Port, &GPIO_InitStruct);

  /*Configure GPIO pins : PA7 PA15 */
  GPIO_InitStruct.Pin = GPIO_PIN_7|GPIO_PIN_15;
  GPIO_InitStruct.Mode = GPIO_MODE_ANALOG;
  GPIO_InitStruct.Pull = GPIO_NOPULL;
  HAL_GPIO_Init(GPIOA, &GPIO_InitStruct);

  /*Configure GPIO pins : PB0 PB1 PB2 PB12
                           PB13 PB14 PB15 PB3
                           PB4 PB5 PB6 PB7
                           PB8 PB9 */
  GPIO_InitStruct.Pin = GPIO_PIN_0|GPIO_PIN_1|GPIO_PIN_2|GPIO_PIN_12
                          |GPIO_PIN_13|GPIO_PIN_14|GPIO_PIN_15|GPIO_PIN_3
                          |GPIO_PIN_4|GPIO_PIN_5|GPIO_PIN_6|GPIO_PIN_7
                          |GPIO_PIN_8|GPIO_PIN_9;
  GPIO_InitStruct.Mode = GPIO_MODE_ANALOG;
  GPIO_InitStruct.Pull = GPIO_NOPULL;
  HAL_GPIO_Init(GPIOB, &GPIO_InitStruct);

  /*Configure GPIO pins : PG0 PG1 PG2 PG3
                           PG4 PG5 PG8 PG9
                           PG10 PG11 PG12 PG13
                           PG14 PG15 */
  GPIO_InitStruct.Pin = GPIO_PIN_0|GPIO_PIN_1|GPIO_PIN_2|GPIO_PIN_3
                          |GPIO_PIN_4|GPIO_PIN_5|GPIO_PIN_8|GPIO_PIN_9
                          |GPIO_PIN_10|GPIO_PIN_11|GPIO_PIN_12|GPIO_PIN_13
                          |GPIO_PIN_14|GPIO_PIN_15;
  GPIO_InitStruct.Mode = GPIO_MODE_ANALOG;
  GPIO_InitStruct.Pull = GPIO_NOPULL;
  HAL_GPIO_Init(GPIOG, &GPIO_InitStruct);

  /*Configure GPIO pin : PtPin */
  GPIO_InitStruct.Pin = IMU_RXD_Pin;
  GPIO_InitStruct.Mode = GPIO_MODE_AF_PP;
  GPIO_InitStruct.Pull = GPIO_NOPULL;
  GPIO_InitStruct.Speed = GPIO_SPEED_FREQ_VERY_HIGH;
  GPIO_InitStruct.Alternate = GPIO_AF7_USART3;
  HAL_GPIO_Init(IMU_RXD_GPIO_Port, &GPIO_InitStruct);

  /*Configure GPIO pin : PtPin */
  GPIO_InitStruct.Pin = IMU_TXD_Pin;
  GPIO_InitStruct.Mode = GPIO_MODE_AF_PP;
  GPIO_InitStruct.Pull = GPIO_PULLUP;
  GPIO_InitStruct.Speed = GPIO_SPEED_FREQ_VERY_HIGH;
  GPIO_InitStruct.Alternate = GPIO_AF7_USART3;
  HAL_GPIO_Init(IMU_TXD_GPIO_Port, &GPIO_InitStruct);

  /*Configure GPIO pins : PD8 PD9 PD10 PD11
                           PD12 PD13 PD14 PD15
                           PD0 PD1 PD2 PD3
                           PD4 PD5 PD6 PD7 */
  GPIO_InitStruct.Pin = GPIO_PIN_8|GPIO_PIN_9|GPIO_PIN_10|GPIO_PIN_11
                          |GPIO_PIN_12|GPIO_PIN_13|GPIO_PIN_14|GPIO_PIN_15
                          |GPIO_PIN_0|GPIO_PIN_1|GPIO_PIN_2|GPIO_PIN_3
                          |GPIO_PIN_4|GPIO_PIN_5|GPIO_PIN_6|GPIO_PIN_7;
  GPIO_InitStruct.Mode = GPIO_MODE_ANALOG;
  GPIO_InitStruct.Pull = GPIO_NOPULL;
  HAL_GPIO_Init(GPIOD, &GPIO_InitStruct);

}

/* USER CODE BEGIN 2 */

/* USER CODE END 2 */

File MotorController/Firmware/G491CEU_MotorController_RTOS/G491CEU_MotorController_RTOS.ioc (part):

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Mcu.Name=STM32G491C(C-E)Ux
Mcu.Package=UFQFPN48
Mcu.UserName=STM32G491CEUx
PA0.GPIOParameters=GPIO_PuPd,GPIO_Label
PA0.GPIO_Label=COCK_ENC_A
PA0.GPIO_PuPd=GPIO_PULLUP
PA0.Signal=S_TIM2_CH1
PA1.GPIOParameters=GPIO_Label
PA1.GPIO_Label=IMU_DE
PA1.Signal=USART2_DE
PA10.GPIOParameters=GPIO_PuPd,GPIO_Label
PA10.GPIO_Label=VCP_RX
PA10.GPIO_PuPd=GPIO_PULLUP
PA10.Mode=Asynchronous
PA10.Signal=USART1_RX
PA11.GPIOParameters=GPIO_Speed,GPIO_Label
PA11.GPIO_Label=BUS_RX
PA11.GPIO_Speed=GPIO_SPEED_FREQ_VERY_HIGH
PA11.Mode=FDCAN_Activate
PA11.Signal=FDCAN1_RX
PA12.GPIOParameters=GPIO_Speed,GPIO_Label
PA12.GPIO_Label=BUS_TX
PA12.GPIO_Speed=GPIO_SPEED_FREQ_VERY_HIGH
PA12.Mode=FDCAN_Activate
PA12.Signal=FDCAN1_TX
PA13.Mode=Serial_Wire
PA13.Signal=SYS_JTMS-SWDIO
PA14.Mode=Serial_Wire
PA14.Signal=SYS_JTCK-SWCLK
PA15.GPIOParameters=PinState,GPIO_PuPd,GPIO_Label,GPIO_ModeDefaultOutputPP
PA15.GPIO_Label=TRIGGER_ENABLE
PA15.GPIO_ModeDefaultOutputPP=GPIO_MODE_OUTPUT_PP
PA15.GPIO_PuPd=GPIO_NOPULL
PA15.PinState=GPIO_PIN_RESET
PA15.Signal=GPIO_Output
PA2.GPIOParameters=GPIO_Label
PA2.GPIO_Label=IMU_RX
PA2.Signal=USART2_TX
PA3.GPIOParameters=GPIO_PuPd,GPIO_Label
PA3.GPIO_Label=IMU_TX
PA3.GPIO_PuPd=GPIO_PULLUP
PA3.Signal=USART2_RX
PA4.GPIOParameters=GPIO_Label
PA4.GPIO_Label=COCK_PWR_RETRACT
PA4.Signal=S_TIM3_CH2
PA5.GPIOParameters=GPIO_PuPd,GPIO_Label
PA5.GPIO_Label=COCK_PWR_EN
PA5.GPIO_PuPd=GPIO_PULLDOWN
PA5.Signal=GPIO_Output
PA6.GPIOParameters=GPIO_Label
PA6.GPIO_Label=COCK_PWR_ERECT
PA6.Signal=S_TIM3_CH1
PA7.GPIOParameters=GPIO_PuPd,GPIO_Label,GPIO_ModeDefaultEXTI
PA7.GPIO_Label=LIM_AZ_ZERO
PA7.GPIO_ModeDefaultEXTI=GPIO_MODE_IT_RISING_FALLING
PA7.GPIO_PuPd=GPIO_PULLUP
PA7.Signal=GPXTI7
PA9.GPIOParameters=GPIO_Label
PA9.GPIO_Label=VCP_TX
PA9.Mode=Asynchronous
PA9.Signal=USART1_TX
PB11.GPIOParameters=GPIO_PuPd,GPIO_Label,GPIO_ModeDefaultEXTI
PB11.GPIO_Label=MUNC_A
PB11.GPIO_ModeDefaultEXTI=GPIO_MODE_IT_FALLING
PB11.GPIO_PuPd=GPIO_PULLUP
PB11.Signal=GPXTI11
PB12.GPIOParameters=GPIO_PuPd,GPIO_Label,GPIO_ModeDefaultEXTI
PB12.GPIO_Label=MUNC_B
PB12.GPIO_ModeDefaultEXTI=GPIO_MODE_IT_FALLING
PB12.GPIO_PuPd=GPIO_PULLUP
PB12.Signal=GPXTI12
PB14.GPIOParameters=GPIO_PuPd,GPIO_Label
PB14.GPIO_Label=T_JS_PULSE
PB14.GPIO_PuPd=GPIO_PULLUP
PB14.Signal=GPIO_Input
PB15.GPIOParameters=GPIO_Label
PB15.GPIO_Label=T_START
PB15.Signal=GPIO_Output
PB3.GPIOParameters=GPIO_PuPd,GPIO_Label
PB3.GPIO_Label=COCK_ENC_B
PB3.GPIO_PuPd=GPIO_PULLUP
PB3.Signal=S_TIM2_CH2
PB5.GPIOParameters=GPIO_Speed,GPIO_Label
PB5.GPIO_Label=MOTOR_RX
PB5.GPIO_Speed=GPIO_SPEED_FREQ_VERY_HIGH
PB5.Mode=FDCAN_Activate
PB5.Signal=FDCAN2_RX
PB6.GPIOParameters=GPIO_Speed,GPIO_Label
PB6.GPIO_Label=MOTOR_TX
PB6.GPIO_Speed=GPIO_SPEED_FREQ_VERY_HIGH
PB6.Mode=FDCAN_Activate
PB6.Signal=FDCAN2_TX
PB8-BOOT0.GPIOParameters=GPIO_PuPd,GPIO_Label
PB8-BOOT0.GPIO_Label=BOOT0
PB8-BOOT0.GPIO_PuPd=GPIO_PULLDOWN
PB8-BOOT0.Signal=GPIO_Input
PB9.GPIOParameters=PinState,GPIO_Label
PB9.GPIO_Label=LED_BUILTIN
PB9.PinState=GPIO_PIN_SET
PB9.Signal=GPIO_Output
PC13.Signal=SYS_WKUP2
PC6.GPIOParameters=GPIO_Label
PC6.GPIO_Label=T_HOLD
PC6.Signal=GPIO_Output
PF0-OSC_IN.Mode=HSE-External-Oscillator
PF0-OSC_IN.Signal=RCC_OSC_IN
PF1-OSC_OUT.Mode=HSE-External-Oscillator
PF1-OSC_OUT.Signal=RCC_OSC_OUT
PG10-NRST.GPIOParameters=GPIO_PuPd,GPIO_Label
PG10-NRST.GPIO_Label=NRST
PG10-NRST.GPIO_PuPd=GPIO_PULLUP
PG10-NRST.Signal=GPIO_Input
RCC.HSE_VALUE=8000000
RCC.SYSCLKFreq_VALUE=170000000
RCC.SYSCLKSource=RCC_SYSCLKSOURCE_PLLCLK
board=custom

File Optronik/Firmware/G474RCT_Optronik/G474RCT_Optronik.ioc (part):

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Mcu.Name=STM32G474R(B-C-E)Tx
Mcu.Package=LQFP64
Mcu.UserName=STM32G474RCTx
PA10.GPIOParameters=GPIO_Speed,GPIO_PuPd,GPIO_Label
PA10.GPIO_Label=VCP_RX
PA10.GPIO_PuPd=GPIO_PULLUP
PA10.GPIO_Speed=GPIO_SPEED_FREQ_VERY_HIGH
PA10.Mode=Asynchronous
PA10.Signal=USART1_RX
PA11.GPIOParameters=GPIO_Speed,GPIO_PuPd
PA11.GPIO_PuPd=GPIO_PULLUP
PA11.GPIO_Speed=GPIO_SPEED_FREQ_VERY_HIGH
PA11.Signal=FDCAN1_RX
PA12.Signal=FDCAN1_TX
PA13.Mode=Serial_Wire
PA13.Signal=SYS_JTMS-SWDIO
PA14.Mode=Serial_Wire
PA14.Signal=SYS_JTCK-SWCLK
PA15.GPIOParameters=GPIO_Label
PA15.GPIO_Label=THERMAL_ENABLE
PA15.Signal=GPIO_Output
PA2.Signal=QUADSPI1_BK1_NCS
PA3.Signal=QUADSPI1_CLK
PA6.Signal=QUADSPI1_BK1_IO3
PA7.Signal=QUADSPI1_BK1_IO2
PA9.GPIOParameters=GPIO_Speed,GPIO_PuPd,GPIO_Label
PA9.GPIO_Label=VCP_TX
PA9.GPIO_PuPd=GPIO_PULLUP
PA9.GPIO_Speed=GPIO_SPEED_FREQ_VERY_HIGH
PA9.Mode=Asynchronous
PA9.Signal=USART1_TX
PB0.Signal=QUADSPI1_BK1_IO1
PB1.Signal=QUADSPI1_BK1_IO0
PB14.GPIOParameters=PinState,GPIO_Label,GPIO_ModeDefaultOutputPP
PB14.GPIO_Label=LED_BUILTIN
PB14.GPIO_ModeDefaultOutputPP=GPIO_MODE_OUTPUT_PP
PB14.PinState=GPIO_PIN_SET
PB14.Signal=GPIO_Output
PB3.GPIOParameters=GPIO_Speed,GPIO_PuPd,GPIO_Label
PB3.GPIO_Label=SONY_RXD
PB3.GPIO_PuPd=GPIO_NOPULL
PB3.GPIO_Speed=GPIO_SPEED_FREQ_VERY_HIGH
PB3.Mode=Asynchronous
PB3.Signal=USART2_TX
PB4.GPIOParameters=GPIO_Speed,GPIO_PuPd,GPIO_Label
PB4.GPIO_Label=SONY_TXD
PB4.GPIO_PuPd=GPIO_PULLUP
PB4.GPIO_Speed=GPIO_SPEED_FREQ_VERY_HIGH
PB4.Mode=Asynchronous
PB4.Signal=USART2_RX
PB8-BOOT0.GPIOParameters=GPIO_Label
PB8-BOOT0.GPIO_Label=Boot0
PB8-BOOT0.Signal=GPIO_Input
PC0.GPIOParameters=GPIO_Speed,GPIO_PuPd,GPIO_Label
PC0.GPIO_Label=LRF_TXD
PC0.GPIO_PuPd=GPIO_PULLUP
PC0.GPIO_Speed=GPIO_SPEED_FREQ_MEDIUM
PC0.Signal=LPUART1_RX
PC1.GPIOParameters=GPIO_Speed,GPIO_PuPd,GPIO_Label
PC1.GPIO_Label=LRF_RXD
PC1.GPIO_PuPd=GPIO_NOPULL
PC1.GPIO_Speed=GPIO_SPEED_FREQ_MEDIUM
PC1.Signal=LPUART1_TX
PC10.GPIOParameters=GPIO_Speed,GPIO_PuPd,GPIO_Label
PC10.GPIO_Label=IMU_RXD
PC10.GPIO_PuPd=GPIO_PULLUP
PC10.GPIO_Speed=GPIO_SPEED_FREQ_VERY_HIGH
PC10.Signal=UART4_TX
PC11.GPIOParameters=GPIO_Speed,GPIO_PuPd,GPIO_Label
PC11.GPIO_Label=IMU_TXD
PC11.GPIO_PuPd=GPIO_PULLUP
PC11.GPIO_Speed=GPIO_SPEED_FREQ_VERY_HIGH
PC11.Signal=UART4_RX
PC12.GPIOParameters=GPIO_Speed,GPIO_PuPd,GPIO_Label
PC12.GPIO_Label=THERMAL_RXD
PC12.GPIO_PuPd=GPIO_PULLUP
PC12.GPIO_Speed=GPIO_SPEED_FREQ_VERY_HIGH
PC12.Signal=UART5_TX
PC13.GPIOParameters=GPIO_PuPd,GPIO_Label
PC13.GPIO_Label=CAMERA_SELECT
PC13.GPIO_PuPd=GPIO_PULLUP
PC13.Signal=GPIO_Output
PC2.GPIOParameters=PinState,GPIO_PuPd,GPIO_Label
PC2.GPIO_Label=LRF_ENABLE
PC2.GPIO_PuPd=GPIO_NOPULL
PC2.PinState=GPIO_PIN_SET
PC2.Signal=GPIO_Output
PD2.GPIOParameters=GPIO_Speed,GPIO_PuPd,GPIO_Label
PD2.GPIO_Label=THERMAL_TXD
PD2.GPIO_PuPd=GPIO_PULLUP
PD2.GPIO_Speed=GPIO_SPEED_FREQ_VERY_HIGH
PD2.Signal=UART5_RX
PF0-OSC_IN.Mode=HSE-External-Oscillator
PF0-OSC_IN.Signal=RCC_OSC_IN
PF1-OSC_OUT.Mode=HSE-External-Oscillator
PF1-OSC_OUT.Signal=RCC_OSC_OUT
RCC.HSE_VALUE=8000000
RCC.SYSCLKFreq_VALUE=170000000
RCC.SYSCLKSource=RCC_SYSCLKSOURCE_PLLCLK
board=custom

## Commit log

2021-06-29 initial skeleton firmware
2021-08-24 skeleton firmware
2021-12-01 misc update
2022-07-08 beta release 0.1.1
    - optronik perlu di tuning lagi rtos nya
    - motor control juga
    - panel musti di rtos kan
2022-07-15 tuning rtos motorControl
2022-07-15 cleaning
2022-07-15 Clean up ignored files/folders
2022-07-15 Clean up ignored files/folders again
2022-07-15 cleaning again
    Preparing the Cleanup:
    -------------------------
    Before cleaning up your repository, you should conduct two important preparations:
    1. Make sure your .gitignore file is up-to-date and contains all the correct patterns you want to ignore.
    2. Commit or stash any outstanding local changes you might have. Your working copy should be clean before you continue.
    Cleaning Ignored Files:
2022-07-20 major: add munition counter
    also update motorController
